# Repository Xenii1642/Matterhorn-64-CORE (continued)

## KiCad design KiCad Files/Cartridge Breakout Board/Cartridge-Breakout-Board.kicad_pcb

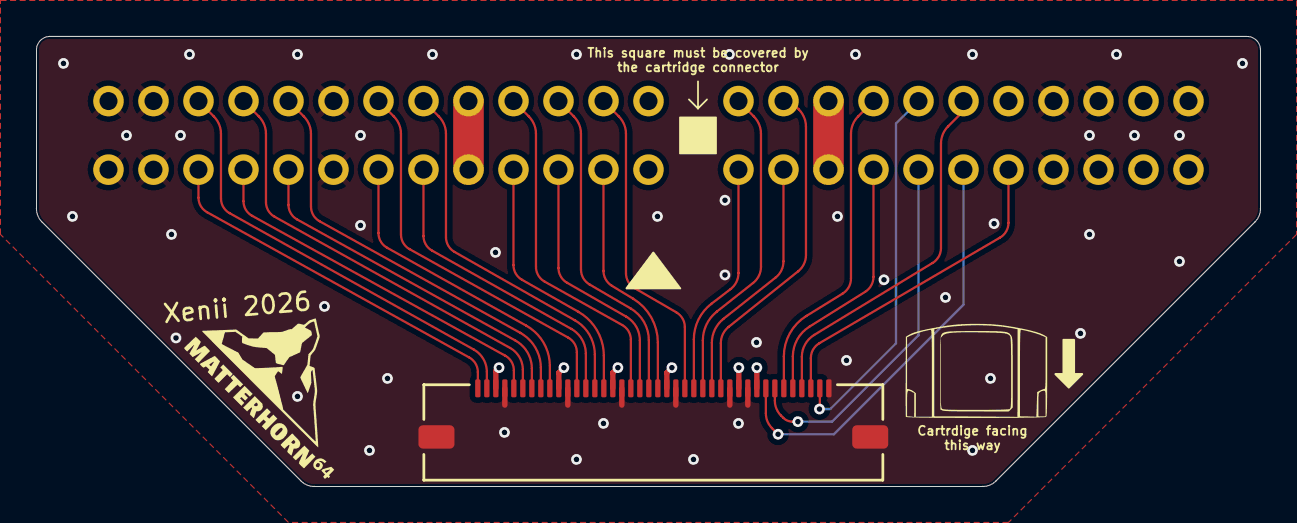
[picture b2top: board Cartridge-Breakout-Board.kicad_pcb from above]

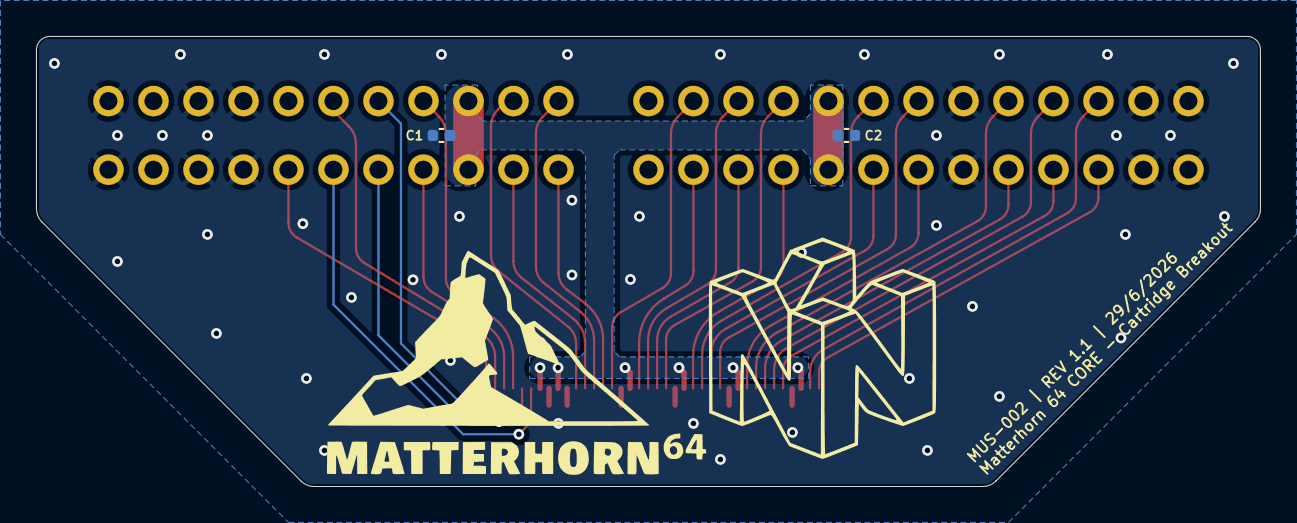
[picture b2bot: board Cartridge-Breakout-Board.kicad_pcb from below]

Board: 2 copper layers, 68.0 x 25.0 mm, 4 parts (2 on the bottom side), 29 nets.

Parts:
C1, C2: 10µF; C_0402_1005Metric
J1: CON_5051104091_MOL
U1: cartridge-slot

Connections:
+3V3: C1.1, C2.1, J1.9, J1.11, J1.19, J1.25, J1.31, J1.38, U1.9 (VCC), U1.17 (VCC), U1.34 (VCC), U1.42 (VCC)
/CAD0: J1.39, U1.28 (AD0)
/CAD1: J1.35, U1.29 (AD1)
/CAD2: J1.33, U1.30 (AD2)
/CAD3: J1.29, U1.32 (AD3)
/CAD4: J1.21, U1.36 (AD4)
/CAD5: J1.17, U1.37 (AD5)
/CAD6: J1.15, U1.40 (AD6)
/CAD7: J1.13, U1.41 (AD7)
/CAD8: J1.14, U1.16 (AD8)
/CAD9: J1.16, U1.15 (AD9)
/CAD10: J1.20, U1.12 (AD10)
/CAD11: J1.22, U1.11 (AD11)
/CAD12: J1.32, U1.7 (AD12)
/CAD13: J1.34, U1.5 (AD13)
/CAD14: J1.36, U1.4 (AD14)
/CAD15: J1.40, U1.3 (AD15)
/CALEH: J1.23, U1.35 (ALEH)
/CALEL: J1.27, U1.33 (ALEL)
/~CRD: J1.26, U1.10 (~RD)
/~CWR: J1.28, U1.8 (~WR)
EXTJOY: J1.3, U1.21 (EXTJOY)
GND: C1.2, C2.2, J1.1, J1.10, J1.12, J1.18, J1.24, J1.30, J1.37, J1.P1, J1.P2, U1.1 (GND), U1.2 (GND), U1.6 (GND), U1.22 (GND), U1.23 (GND), U1.25 (GND), U1.26 (GND), U1.27 (GND), U1.31 (GND), U1.47 (GND), U1.48 (GND), U1.50 (GND)
SECCLK: J1.7, U1.19 (SECCLK)
SECTRO: J1.5, U1.18 (SEC1)
~INT: J1.2, U1.44 (~INT)
~NMI: J1.4, U1.45 (~RESTART)
~RESET: J1.8, U1.20 (~RESET)
~SECTRC: J1.6, U1.43 (SEC2)

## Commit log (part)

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2026-05-14 Add CERN Open Hardware Licence V2
    Added the CERN Open Hardware Licence Version 2 - Strongly Reciprocal to the project.
2026-05-14 Change license to CERN-OHL-S-2.0
    Updated license information from CERN to CERN-OHL-S-2.0.
2026-05-14 Adjust image dimensions in README.md
    Updated image sizes for front and back images in README.
2026-05-14 Rename IMG_6066.JPG to components-removed.JPG
2026-05-14 Rename IMG_6108.JPG to mario64-data.JPG
2026-05-14 Rename IMG_E6008.JPG to size-comparison.JPG
2026-05-14 Update README with media section and image fix
    Added media section with Instagram link and improved image reference.
2026-05-14 Fix typos and enhance readability in README
    Corrected typos and improved clarity in README.
2026-05-14 Fix PCB links and update contributor names
    Updated PCB links and credit names in README.
2026-05-14 Fix typos and improve README clarity
2026-05-14 Fix typos, improve clarity
2026-05-14 forgot this
2026-05-14 fixed my own error
2026-05-14 Members sounds better than people
2026-05-14 fix recommend in other places
2026-05-14 Update README with future projects and credits section
    Added a section about future projects and credits.
2026-05-15 Fix typo in stackup specification
2026-05-16 Adjusted RDRAM bottom traces
2026-05-16 Additionnal details for RDRAM controlled impedance
2026-06-28 Clarify crediting requirements for reused files
    Added a note about crediting original creators when reusing files.
2026-06-29 Updated the cartridge breakout board to REV 1.1
    Changes the cartridge connector which didn't have the correct pitch.
2026-06-29 Updated to REV 1.1
    Changes the cartridge connector for the correct pitch.
2026-06-29 Fixes some mistakes in the footprint library.
    - Corrected the cartridge slot connector with the correct pitch (used by the breakout board REV 1.1)
    - Corrected the pins' numeration of the 74HC125.
